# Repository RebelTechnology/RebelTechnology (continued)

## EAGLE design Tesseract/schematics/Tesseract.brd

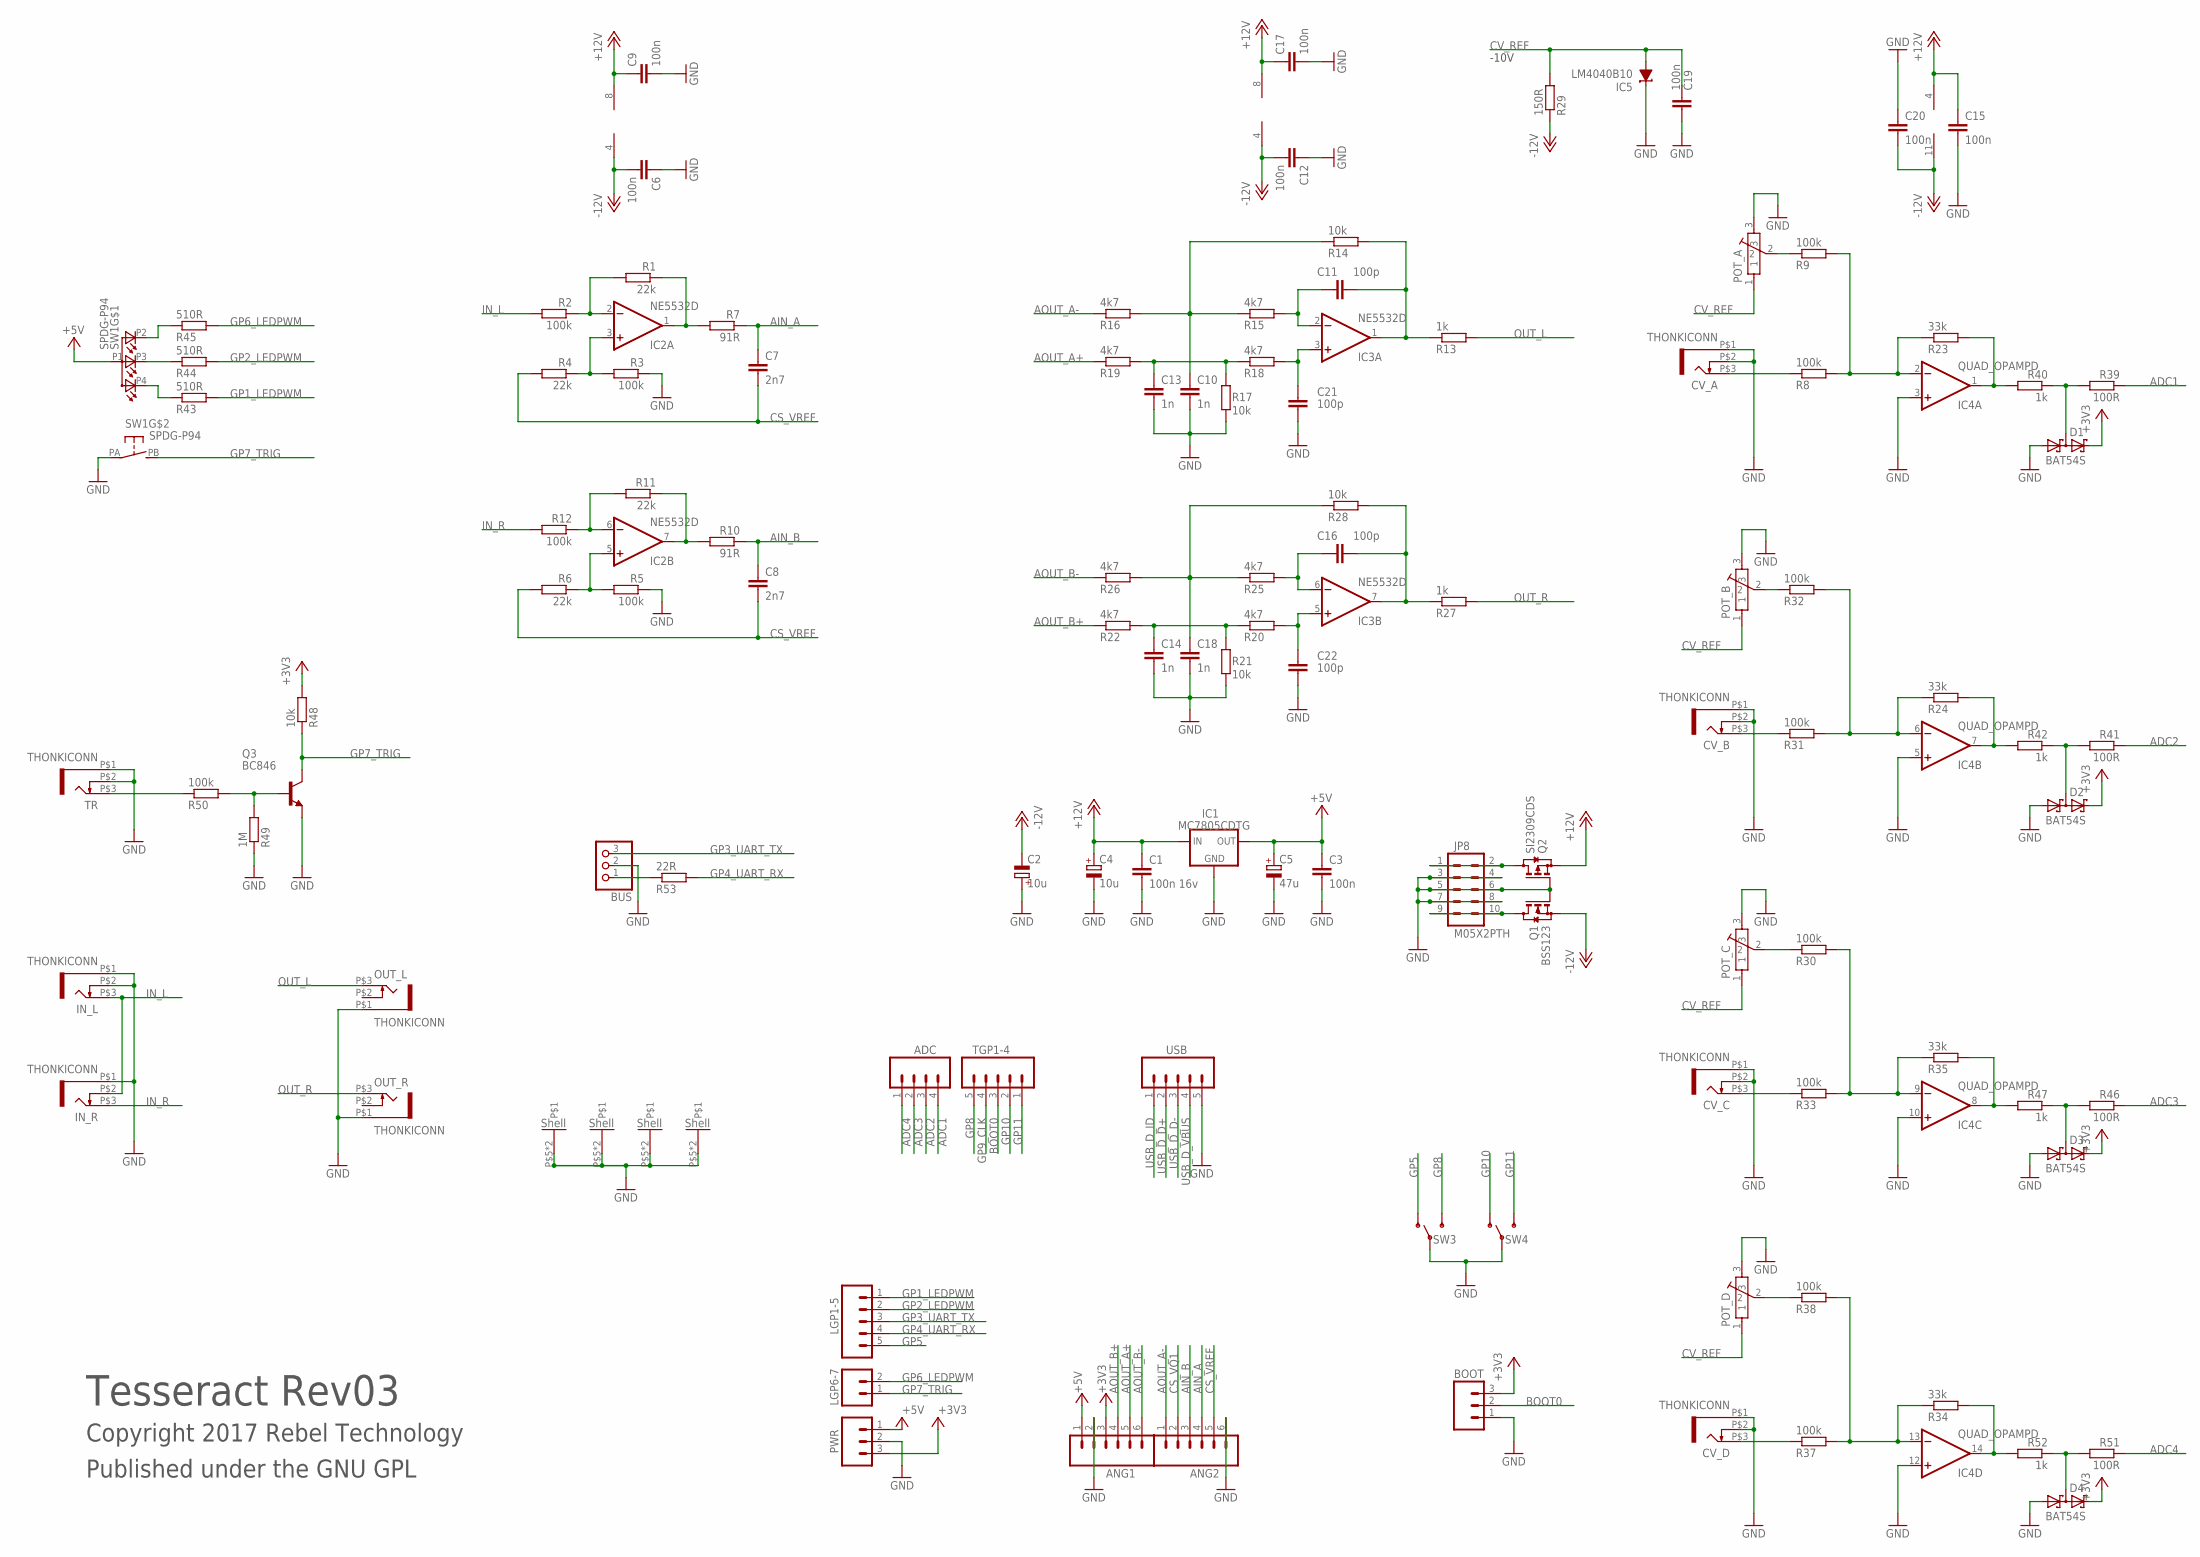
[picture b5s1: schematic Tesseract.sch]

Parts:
ADC: M04PTH; 1X04
ANG1, ANG2: M06SIP; 1X06
BOOT: M03PTH; 1X03
BUS: CON-JST-1X03PH-TH; JST-B3B-PH-KL
C1: 100n 16v; C0603
C2, C4: 10u; CPOL-5
C3, C6, C9, C12, C15, C17, C19, C20: 100n; C0603
C5: 47u; PANASONIC_C
C7, C8: 2n7; C0603
C10, C13, C14, C18: 1n; C0603
C11, C16, C21, C22: 100p; C0603
CV_A: THONKICONN
CV_B: THONKICONN
CV_C: THONKICONN
CV_D: THONKICONN
D1, D2, D3, D4: BAT54S; SOT23
IC1: MC7805CDTG; DPACK
IC2, IC3: NE5532D; SO08
IC4: QUAD_OPAMPD; SO14
IC5: LM4040B10; DBZ_R-PDSO-G3
IN_L: THONKICONN
IN_R: THONKICONN
JP8: M05X2PTH; AVR_ICSP
LGP1-5: M05PTH; 1X05
LGP6-7: M02PTH; 1X02
OUT_L: THONKICONN
OUT_R: THONKICONN
POT_A: POT-ALPS-RK09L1140
POT_B: POT-ALPS-RK09L1140
POT_C: POT-ALPS-RK09L1140
POT_D: POT-ALPS-RK09L1140
PWR: M03PTH; 1X03
Q1: BSS123; SOT23
Q2: SI2309CDS; SOT23
Q3: BC846; SOT23
R1, R4, R6, R11: 22k; 0603
R2, R3, R5, R8, R9, R12, R30, R31, R32, R33, R37, R38, R50: 100k; 0603
R7, R10: 91R; 0603
R13, R27, R40, R42, R47, R52: 1k; 0603
R14, R17, R21, R28, R48: 10k; 0603
R15, R16, R18, R19, R20, R22, R25, R26: 4k7; 0603
R23, R24, R34, R35: 33k; 0603
R29: 150R; 0603
R39, R41, R46, R51: 100R; 0603
R43, R44, R45: 510R; 0603
R49: 1M; 0603
R53: 22R; 0603
SW1: SPDG-P94
SW3, SW4: SUB-MIN-SPDT
TGP1-4: M05PTH; 1X05
TR: THONKICONN
USB: M05PTH; 1X05

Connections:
+3V3: ANG1.3, BOOT.3, D1.2 (C2), D2.2 (C2), D3.2 (C2), D4.2 (C2), PWR.3, R48.2
+5V: ANG1.1, C3.1, C5.+, IC1.3 (OUT), PWR.1, SW1.P1 (A)
+12V: C1.1, C4.+, C9.1, C15.1, C17.1, IC1.1 (IN), IC2.8 (V+), IC3.8 (V+), IC4.4 (V+), Q2.2 (S)
-12V: C2.-, C6.2, C12.2, C20.2, IC2.4 (V-), IC3.4 (V-), IC4.11 (V-), Q1.2 (S), R29.1
ADC1: ADC.4, R39.1
ADC2: ADC.3, R41.1
ADC3: ADC.2, R46.1
ADC4: ADC.1, R51.1
AIN_A: ANG2.4, C7.1, R7.1
AIN_B: ANG2.3, C8.1, R10.1
AOUT_A+: ANG1.5, R19.1
AOUT_A-: ANG2.1, R16.1
AOUT_B+: ANG1.4, R22.1
AOUT_B-: ANG1.6, R26.1
BOOT0: BOOT.2, TGP1-4.3
CS_VQ1: ANG2.2
CS_VREF: ANG2.5, C7.2, C8.2, R4.2, R6.2
CV_REF: C19.1, IC5.2 (A), POT_A.1, POT_B.1, POT_C.1, POT_D.1, R29.2
EXT_UART_RX: BUS.1, R53.1
GND: ANG1.2, ANG2.6, BOOT.1, BUS.2, C1.2, C2.+, C3.2, C4.-, C5.-, C6.1, C9.2, C10.2, C12.1, C13.2, C14.2, C15.2, C17.2, C18.2, C19.2, C20.1, C21.2, C22.2, CV_A.P$1 (5), CV_A.P$2 (4), CV_B.P$1 (5), CV_B.P$2 (4), CV_C.P$1 (5), CV_C.P$2 (4), CV_D.P$1 (5), CV_D.P$2 (4), D1.1 (A1), D2.1 (A1), D3.1 (A1), D4.1 (A1), IC1.4 (GND), IC4.3 (+IN), IC4.5 (+IN), IC4.10 (+IN), IC4.12 (+IN), IC5.1 (C), IN_L.P$1 (5), IN_L.P$2 (4), IN_R.P$1 (5), JP8.3, JP8.4, JP8.5, JP8.6, JP8.7, JP8.8, OUT_L.P$1 (5), OUT_R.P$1 (5), POT_A.3, POT_A.P$5, POT_A.P$6, POT_B.3, POT_B.P$5, POT_B.P$6, POT_C.3, POT_C.P$5, POT_C.P$6, POT_D.3, POT_D.P$5, POT_D.P$6, PWR.2, Q1.1 (G), Q2.1 (G), Q3.2 (E), R3.1, R5.1, R17.1, R21.1, R49.1, SW1.PA, SW3.2, SW4.2, TR.P$1 (5), TR.P$2 (4), USB.5
GP1_LEDPWM: LGP1-5.1, R43.2
GP2_LEDPWM: LGP1-5.2, R44.2
GP3_UART_TX: BUS.3, LGP1-5.3
GP4_UART_RX: LGP1-5.4, R53.2
GP5: LGP1-5.5, SW3.1 (O)
GP6_LEDPWM: LGP6-7.2, R45.2
GP7_TRIG: LGP6-7.1, Q3.3 (C), R48.1, SW1.PB (S)
GP8: SW3.3 (S), TGP1-4.5
GP9_CLK: TGP1-4.4
GP10: SW4.1 (O), TGP1-4.2
GP11: SW4.3 (S), TGP1-4.1
IN_L: IN_L.P$3 (3), IN_R.P$2 (4), R2.2
IN_R: IN_R.P$3 (3), R12.2
unnamed: IC2.1 (OUT), R1.1, R7.2
unnamed: IC2.3 (+IN), R3.2, R4.1
unnamed: CV_A.P$3 (3), R8.1
unnamed: IC2.5 (+IN), R5.2, R6.1
unnamed: IC2.6 (-IN), R11.2, R12.1
unnamed: IC4.9 (-IN), R30.2, R33.2, R35.1
unnamed: C11.1, IC3.2 (-IN), R15.2
unnamed: JP8.9, JP8.10, Q1.3 (D)
unnamed: IC2.2 (-IN), R1.2, R2.1
unnamed: IC2.7 (OUT), R10.2, R11.1
unnamed: C21.1, IC3.3 (+IN), R18.2
unnamed: JP8.1, JP8.2, Q2.3 (D)
unnamed: IC4.2 (-IN), R8.2, R9.2, R23.1
unnamed: POT_A.2, R9.1
unnamed: C13.1, R17.2, R18.1, R19.2
unnamed: D1.3 (C1A2), R39.2, R40.1
unnamed: IC4.1 (OUT), R23.2, R40.2
unnamed: C16.2, IC3.7 (OUT), R27.1, R28.2
unnamed: CV_B.P$3 (3), R31.1
unnamed: IC4.6 (-IN), R24.1, R31.2, R32.2
unnamed: POT_B.2, R32.1
unnamed: IC4.7 (OUT), R24.2, R42.2
unnamed: D2.3 (C1A2), R41.2, R42.1
unnamed: C18.1, R25.1, R26.2, R28.1
unnamed: CV_C.P$3 (3), R33.1
unnamed: C16.1, IC3.6 (-IN), R25.2
unnamed: POT_C.2, R30.1
unnamed: IC4.8 (OUT), R35.2, R47.2
unnamed: D3.3 (C1A2), R46.2, R47.1
unnamed: C22.1, IC3.5 (+IN), R20.2
unnamed: CV_D.P$3 (3), R37.1
unnamed: C14.1, R20.1, R21.2, R22.2
unnamed: IC4.13 (-IN), R34.1, R37.2, R38.2
unnamed: POT_D.2, R38.1
unnamed: IC4.14 (OUT), R34.2, R52.2
unnamed: D4.3 (C1A2), R51.2, R52.1
unnamed: Q3.1 (B), R49.2, R50.2
unnamed: C11.2, IC3.1 (OUT), R13.1, R14.2
unnamed: R43.1, SW1.P4 (CRED)
unnamed: C10.1, R14.1, R15.1, R16.2
unnamed: R45.1, SW1.P2 (CGREEN)
unnamed: R44.1, SW1.P3 (CBLUE)
unnamed: R50.1, TR.P$3 (3)
OUT_L: OUT_L.P$3 (3), R13.2
OUT_R: OUT_R.P$3 (3), R27.2
USB_D_D+: USB.2
USB_D_D-: USB.3
USB_D_ID: USB.1
USB_D_VBUS: USB.4

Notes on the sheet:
Tesseract Rev03
Copyright 2017 Rebel Technology
Published under the GNU GPL
-10V

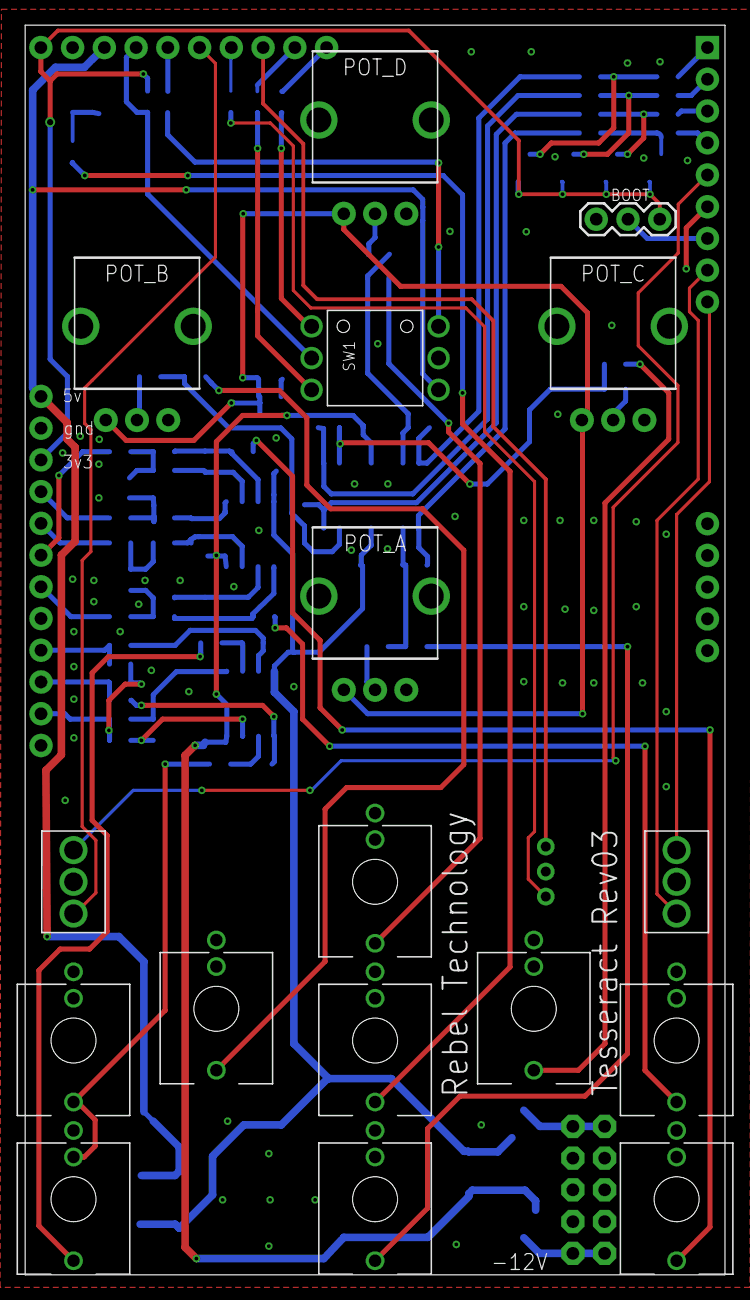
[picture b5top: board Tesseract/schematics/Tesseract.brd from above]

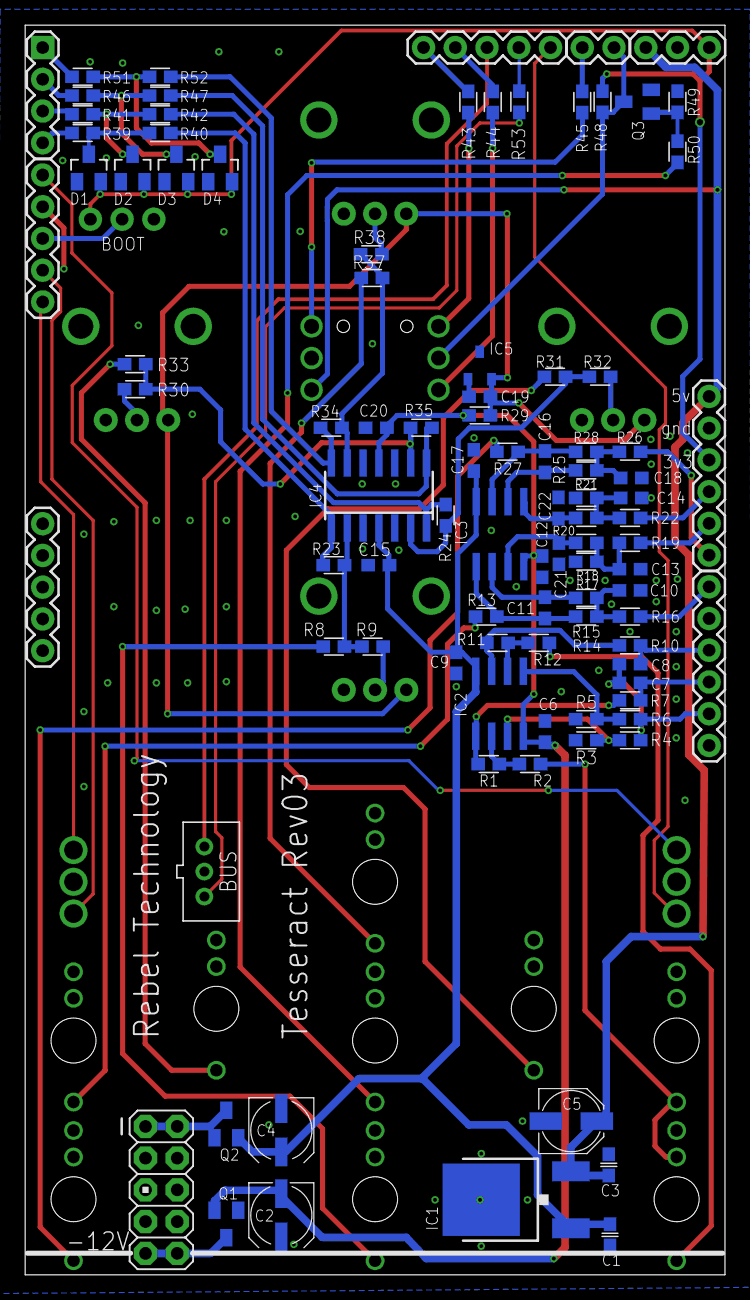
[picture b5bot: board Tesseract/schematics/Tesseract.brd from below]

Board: 2 copper layers, 56.0 x 100.0 mm, 113 parts (96 on the bottom side), 76 nets.

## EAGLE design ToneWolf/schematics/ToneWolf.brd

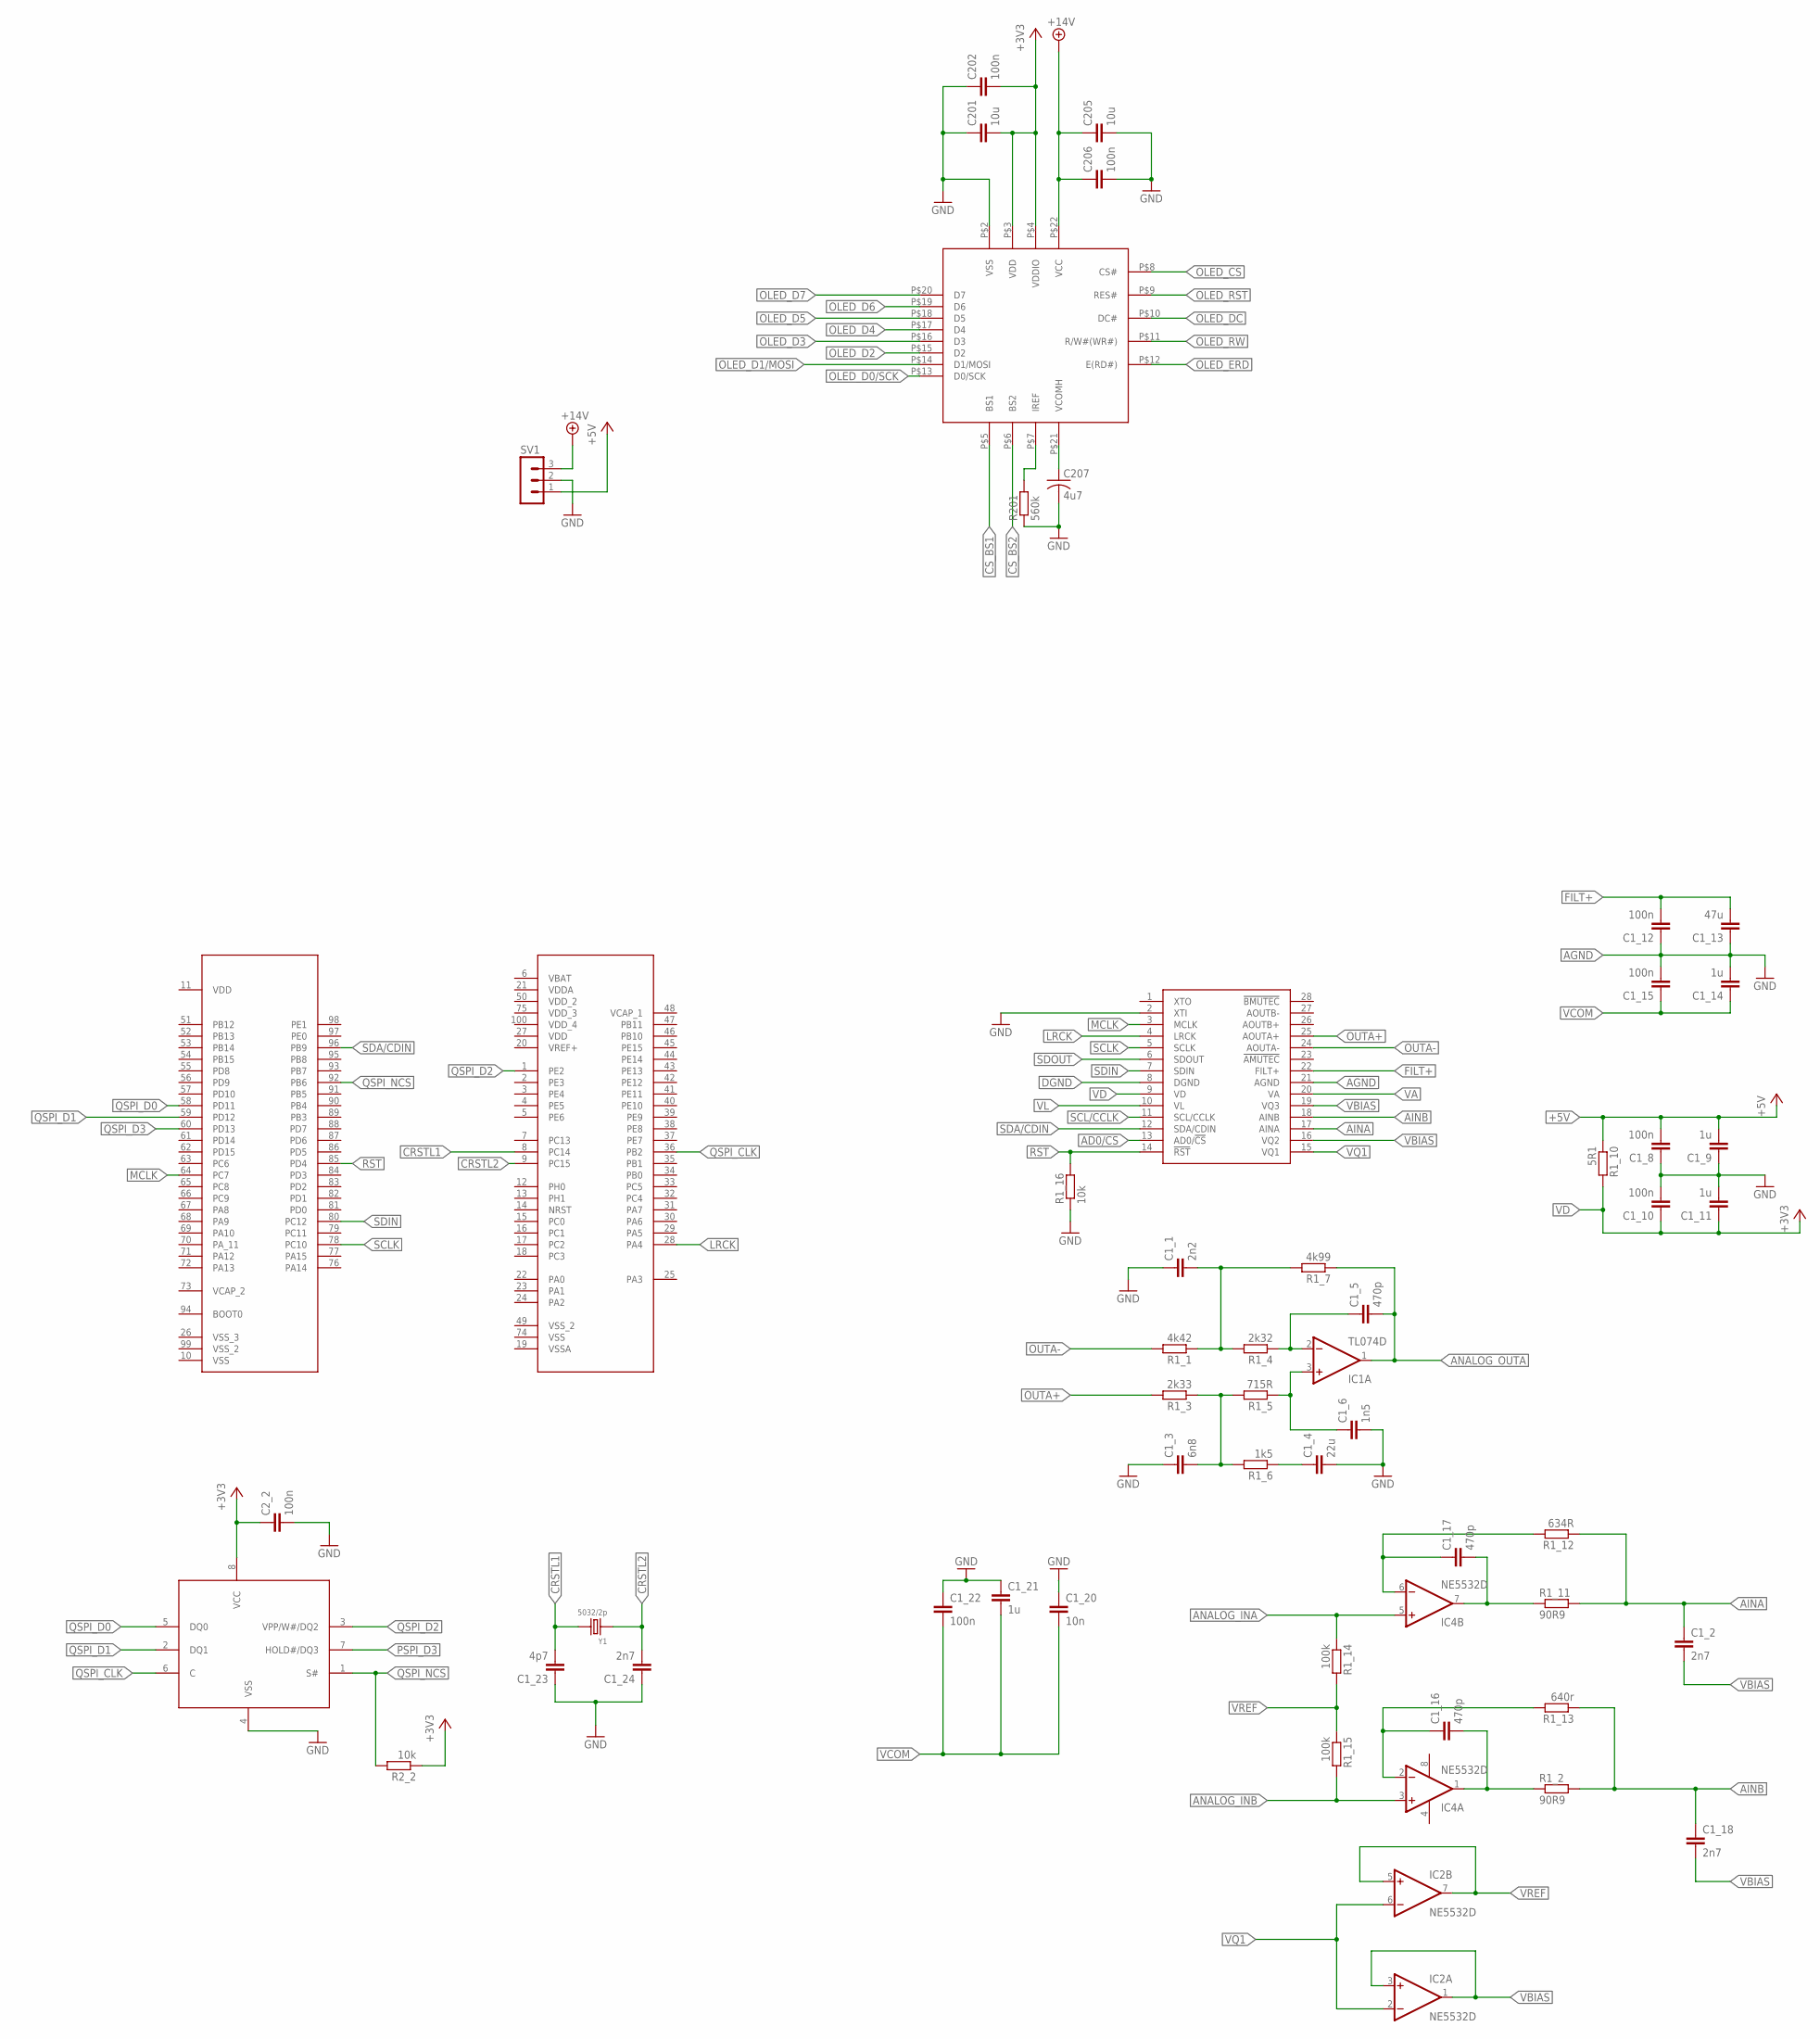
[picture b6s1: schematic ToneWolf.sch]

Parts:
C1_1: 2n2; C0603
C1_2, C1_18, C1_24: 2n7; C0603
C1_3: 6n8; C0603
C1_4: 22u; C0603
C1_5, C1_16, C1_17: 470p; C0603
C1_6: 1n5; C0603
C1_8, C1_10, C1_12, C1_15, C1_22, C2_2, C202, C206: 100n; C0603
C1_9, C1_11, C1_14, C1_21: 1u; C0603
C1_13: 47u; C0603
C1_20: 10n; C0603
C1_23: 4p7; C0603
C201, C205: 10u; C0603
C207: 4u7; C0603
IC1: TL074D; SO14
IC2, IC4: NE5532D; SO08
R1_1: 4k42; R0603
R1_2, R1_11: 90R9; R0603
R1_3: 2k33; R0603
R1_4: 2k32; R0603
R1_5: 715R; R0603
R1_6: 1k5; R0603
R1_7: 4k99; R0603
R1_10: 5R1; R0603
R1_12: 634R; R0603
R1_13: 640r; R0603
R1_14, R1_15: 100k; R0603
R1_16, R2_2: 10k; R0603
R201: 560k; R0603
SV1: MA03-1
U$3: MCOT096064AZ-RGBM
U$4: CS4271; TSSOP28-0.65-9.7X4.4MM
U$5: STM32F746VGT6; QFP50P1600X1600X160-100N
U$6: N25Q128A13; SO8W
Y1: 5032/2p; X2-SMD-5.0X3.2X1.3MM

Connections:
+3V3: C2_2.1, C201.2, C202.2, R2_2.1, U$3.P$3 (VDD), U$3.P$4 (VDDIO), U$6.8 (VCC)
+5V: C1_8.2, C1_9.2, R1_10.1, SV1.1
+14V: C205.1, C206.1, SV1.3, U$3.P$22 (VCC)
AD0/CS: U$4.13 (AD0/!CS)
AGND: C1_12.1, C1_13.1, C1_14.2, C1_15.2, U$4.21 (AGND)
AINA: C1_2.1, R1_11.2, R1_12.1, U$4.17 (AINA)
AINB: C1_18.1, R1_2.2, R1_13.1, U$4.18 (AINB)
ANALOG_INA: IC4.5 (+IN), R1_14.1
ANALOG_INB: IC4.3 (+IN), R1_15.2
ANALOG_OUTA: C1_5.2, IC1.1 (OUT), R1_7.1
CRSTL1: C1_23.2, U$5.8 (PC14), Y1.2
CRSTL2: C1_24.2, U$5.9 (PC15), Y1.1
CS_BS1: U$3.P$5 (BS1)
CS_BS2: U$3.P$6 (BS2)
DGND: U$4.8 (DGND)
FILT+: C1_12.2, C1_13.2, U$4.22 (FILT+)
GND: C1_1.1, C1_3.1, C1_4.2, C1_6.2, C1_8.1, C1_9.1, C1_10.2, C1_11.2, C1_20.1, C1_21.1, C1_22.1, C1_23.1, C1_24.1, C2_2.2, C201.1, C202.1, C205.2, C206.2, C207.2, R1_16.1, R201.1, SV1.2, U$3.P$2 (VSS), U$4.2 (XTI), U$6.4 (VSS)
LRCK: U$4.4 (LRCK), U$5.28 (PA4)
MCLK: U$4.3 (MCLK), U$5.64 (PC7)
unnamed: C1_3.2, R1_3.1, R1_5.2, R1_6.2
unnamed: C207.1, U$3.P$21 (VCOMH)
unnamed: R201.2, U$3.P$7 (IREF)
unnamed: C1_1.2, R1_1.1, R1_4.2, R1_7.2
unnamed: C1_4.1, R1_6.1
unnamed: C1_5.1, IC1.2 (-IN), R1_4.1
unnamed: C1_6.1, IC1.3 (+IN), R1_5.1
unnamed: C1_16.2, IC4.1 (OUT), R1_2.1
unnamed: C1_17.2, IC4.7 (OUT), R1_11.1
unnamed: C1_16.1, IC4.2 (-IN), R1_13.2
unnamed: C1_17.1, IC4.6 (-IN), R1_12.2
OLED_CS: U$3.P$8 (CS#)
OLED_D0/SCK: U$3.P$13 (D0/SCK)
OLED_D1/MOSI: U$3.P$14 (D1/MOSI)
OLED_D2: U$3.P$15 (D2)
OLED_D3: U$3.P$16 (D3)
OLED_D4: U$3.P$17 (D4)
OLED_D5: U$3.P$18 (D5)
OLED_D6: U$3.P$19 (D6)
OLED_D7: U$3.P$20 (D7)
OLED_DC: U$3.P$10 (DC#)
OLED_ERD: U$3.P$12 (E(RD#))
OLED_RST: U$3.P$9 (RES#)
OLED_RW: U$3.P$11 (R/W#(WR#))
OUTA+: R1_3.2, U$4.25 (AOUTA+)
OUTA-: R1_1.2, U$4.24 (AOUTA-)
PSPI_D3: U$6.7 (HOLD#/DQ3)
QSPI_CLK: U$5.36 (PB2), U$6.6 (C)
QSPI_D0: U$5.58 (PD11), U$6.5 (DQ0)
QSPI_D1: U$5.59 (PD12), U$6.2 (DQ1)
QSPI_D2: U$5.1 (PE2), U$6.3 (VPP/W#/DQ2)
QSPI_D3: U$5.60 (PD13)
QSPI_NCS: R2_2.2, U$5.92 (PB6), U$6.1 (S#)
RST: R1_16.2, U$4.14 (!RST), U$5.85 (PD4)
SCL/CCLK: U$4.11 (SCL/CCLK)
SCLK: U$4.5 (SCLK), U$5.78 (PC10)
SDA/CDIN: U$4.12 (SDA/CDIN), U$5.96 (PB9)
SDIN: U$4.7 (SDIN), U$5.80 (PC12)
SDOUT: U$4.6 (SDOUT)
V+: IC1.4 (V+), IC2.8 (V+), IC4.8 (V+)
V-: IC1.11 (V-), IC2.4 (V-), IC4.4 (V-)
VA: U$4.20 (VA)
VBIAS: C1_2.2, C1_18.2, IC2.1 (OUT), IC2.3 (+IN), U$4.16 (VQ2), U$4.19 (VQ3)
VCOM: C1_14.1, C1_15.1, C1_20.2, C1_21.2, C1_22.2
VD: C1_10.1, C1_11.1, R1_10.2, U$4.9 (VD)
VL: U$4.10 (VL)
VQ1: IC2.2 (-IN), IC2.6 (-IN), U$4.15 (VQ1)
VREF: IC2.5 (+IN), IC2.7 (OUT), R1_14.2, R1_15.1

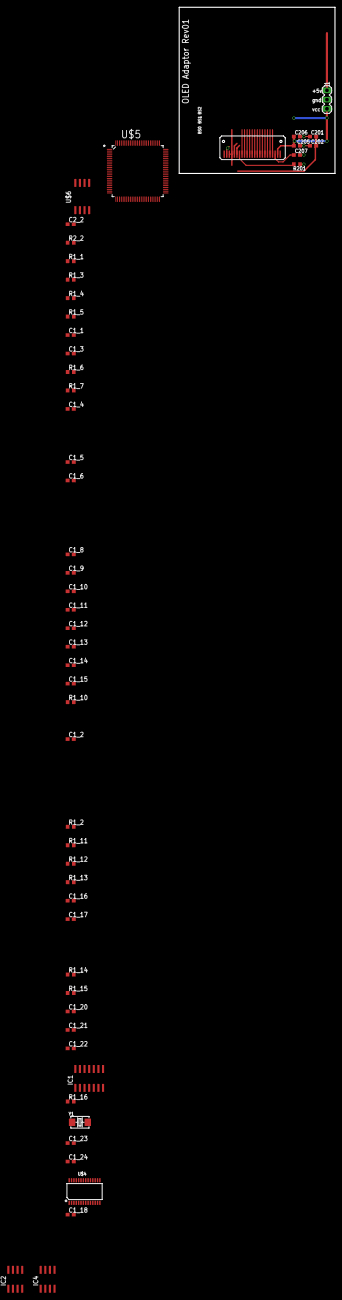
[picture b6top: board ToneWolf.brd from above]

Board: 2 copper layers, 42.9 x 45.7 mm, 53 parts (0 on the bottom side), 44 nets.

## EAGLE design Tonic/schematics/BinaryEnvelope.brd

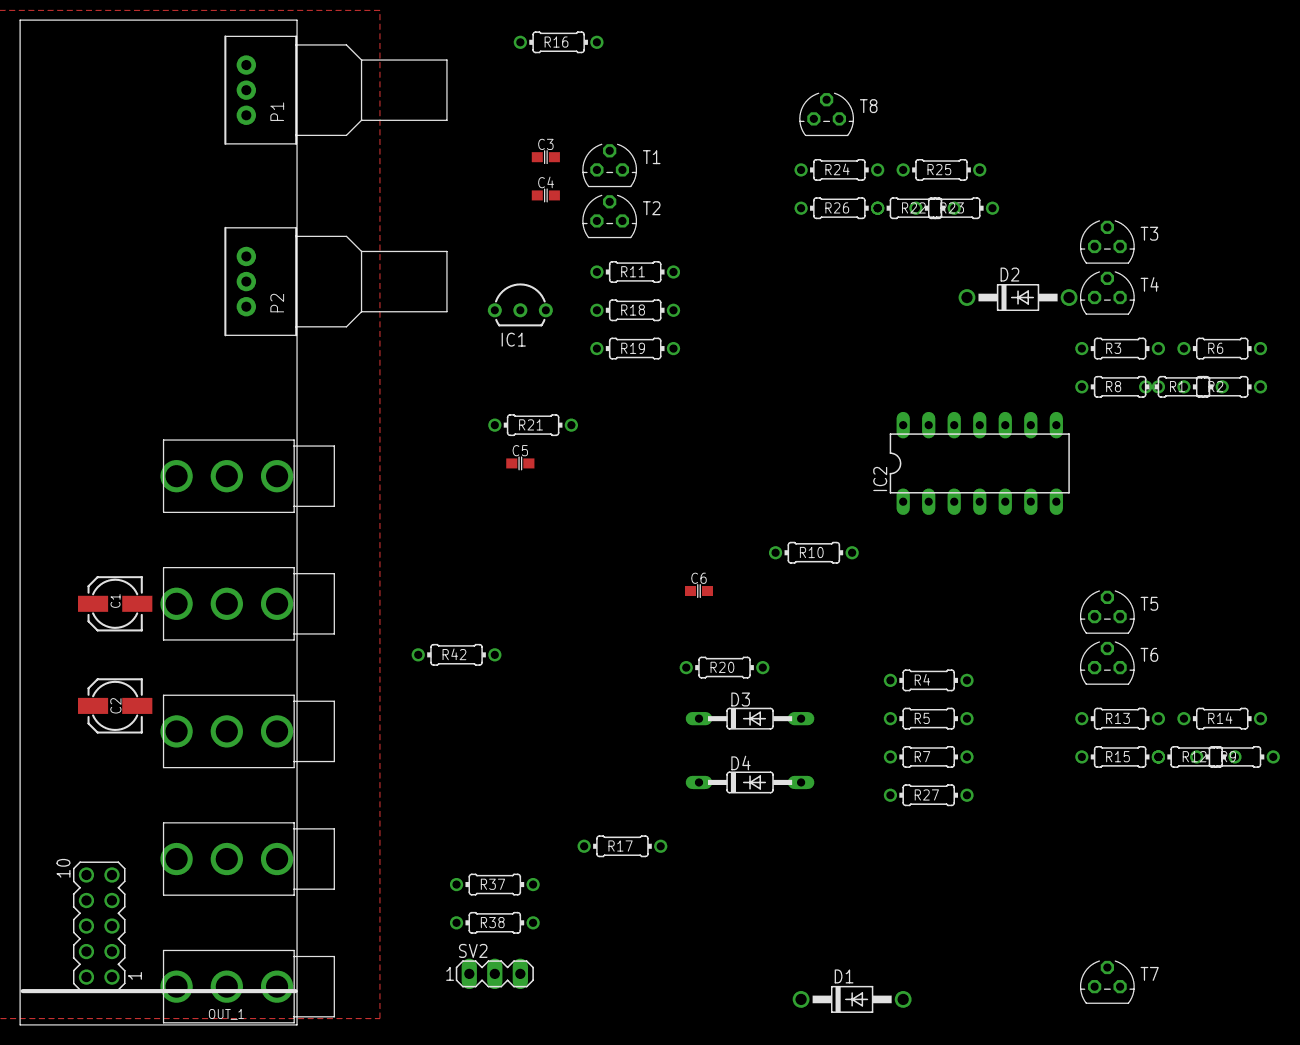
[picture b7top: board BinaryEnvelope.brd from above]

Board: 2 copper layers, 27.6 x 100.0 mm, 59 parts (0 on the bottom side), 38 nets, no tracks yet.

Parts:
C1, C2: 10u; 153CLV-0505
C3, C4, C5: 100n; C0603
C6: 1u; C0603
D1, D2: 1N4004; DO41-10
D3, D4: 1N4148DO35-10; DO35-10
IC1: LM4040 5V; LP_O-PBCY-W3
IC2: TL074P; DIL14
IN_1, IN_2, IN_3, IN_4: JACK-UJ-3502-R; UJ-3502-R
OUT_1: JACK-UJ-3502-R; UJ-3502-R
P1, P2: POT-BOURNS-PTD901
R1, R6, R8, R9, R14, R15, R18, R19, R25, R26, R27, R37, R38, R42: 10k; 0204/7
R2, R3, R11, R12, R13, R16, R17, R23, R24: 100k; 0204/7
R4, R20: 1k; 0204/7
R5, R22: 2k7; 0204/7
R7: 6k8; 0204/7
R10: 100R; 0204/7
R21: 510R; 0204/7
SV1: MA05-2
SV2: MA03-1
T1, T2, T3, T4, T5, T6, T7, T8: 2N3904; TO92

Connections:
+12V: C1.+, C3.1, D1.C, IC2.4, R8.2, R15.2, R19.2, R21.2, R26.2
-12V: C2.-, C4.1, D2.A, IC2.11
GND: C1.-, C2.+, C3.2, C4.2, C5.2, C6.1, IC1.3, IC2.3, IC2.5, IN_1.P$2, IN_1.P$3, IN_2.P$2, IN_2.P$3, IN_3.P$2, IN_3.P$3, IN_4.P$2, IN_4.P$3, OUT_1.P$2, OUT_1.P$3, R4.1, R5.1, R7.1, R27.1, SV1.3, SV1.4, SV1.5, SV1.6, SV1.7, SV1.8, T1.3, T2.3, T3.3, T4.3, T5.3, T6.3, T7.3, T8.3
unnamed: D2.C, SV1.1, SV1.2
unnamed: IN_1.P$1, R11.1
unnamed: R1.1, R2.2, R5.2, T4.1
unnamed: OUT_1.P$1, R20.1
unnamed: D3.A, D4.C, R10.1
unnamed: IC2.8, R10.2, SV2.3
unnamed: C6.2, IC2.12, P1.1, P1.2, P2.2, P2.3
unnamed: IC2.6, R37.1, R38.2
unnamed: R3.2, T3.2
unnamed: D1.A, SV1.9, SV1.10
unnamed: R6.2, T4.2
unnamed: R6.1, R8.1, T3.1
unnamed: IN_2.P$1, R3.1
unnamed: C5.1, IC1.2, R1.2, R9.2, R21.1, R22.2, R42.2
unnamed: R11.2, T1.2
unnamed: R18.2, T2.2
unnamed: D3.C, P1.3
unnamed: R7.2, R9.1, R12.2, T6.1
unnamed: IC2.13, IC2.14, R20.2, SV2.1
unnamed: R18.1, R19.1, T1.1
unnamed: R13.2, T5.2
unnamed: R14.2, T6.2
unnamed: R14.1, R15.1, T5.1
unnamed: IN_3.P$1, R13.1
unnamed: D4.A, P2.1
unnamed: R22.1, R23.2, R27.2, T8.1
unnamed: IC2.7, IC2.10, R38.1
unnamed: R24.2, T7.2
unnamed: IC2.1, R17.1, R37.2
unnamed: R25.2, T8.2
unnamed: R25.1, R26.1, T7.1
unnamed: IN_4.P$1, R24.1
unnamed: IC2.9, SV2.2
unnamed: R4.2, R16.2, R42.1, T2.1
unnamed: IC2.2, R2.1, R12.1, R16.1, R17.2, R23.1
